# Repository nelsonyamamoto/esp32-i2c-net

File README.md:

# esp32-i2c-net

An ESP32-S3 based IoT data collector with buffered I2C bus over standard
6P6C (RJ12/RJ25) cables, so multiple remote I2C nodes can be wired back to a
single controller using cheap, keyed telephone-style patch cords. The use of
I2C bus driver allow the connection of multiple sensor over long wires.

## Hardware

- **MCU:** ESP32-S3-WROOM-1 (U1)
- **I2C buffering:** PCA9517 level-shifting I2C repeater (U4) plus an
  LTC4311 active rise-time accelerator (U3) to keep edges clean over long
  cable runs
- **Bus ports:** 4× 6P6C modular jacks (J3–J6)
- **USB:** USB-A connector (J1) wired to the ESP32-S3 native USB pins
  (GPIO19 = D−, GPIO20 = D+) for connection of an optional USB device, like a camera.
- **Power:** +5 V input via barrel jack (J2) or USB; AMS1117-3.3 LDO (U2)
  provides the +3.3 V rail
- **Indicators / misc:** WS2812B addressable RGB LED (D1, data on GPIO38),
  reset pushbutton (SW1 on EN), 3.3 V test point (TP1), auxiliary 1×6 header
  (J7) exposing spare GPIOs

### 6P6C port pinout (J3–J6)

| Pin | Signal     |
|-----|------------|
| 1   | GND        |
| 2   | SDA        |
| 3   | +5 V       |
| 4   | +5 V       |
| 5   | SCL        |
| 6   | GND        |
| SH  | Shield/GND |

The buffered bus on the jacks runs at 5 V logic levels (PCA9517 A-side at
+5 V with pull-ups R4/R5); the ESP32 side of the repeater runs at 3.3 V
(GPIO1 = SDA, GPIO2 = SCL, pull-ups R1/R2/R3). The PCA9517 also isolates
the cable capacitance from the MCU bus.

## Repository contents

| File                    | Description                                  |
|-------------------------|----------------------------------------------|
| `esp32-i2c-net.kicad_pro`  | KiCad 7 project file                      |
| `esp32-i2c-net.kicad_sch`  | Schematic                                 |
| `esp32-i2c-net.kicad_pcb`  | PCB layout                                |

## Requirements

- KiCad 7 or later (files use the KiCad 7 schematic/PCB format)

## Status

Work in progress — schematic complete, PCB layout in progress
(DSN exports for the Freerouting autorouter are included).
No firmware in this repository.

## License

No license file is currently included; the design files are provided as-is.

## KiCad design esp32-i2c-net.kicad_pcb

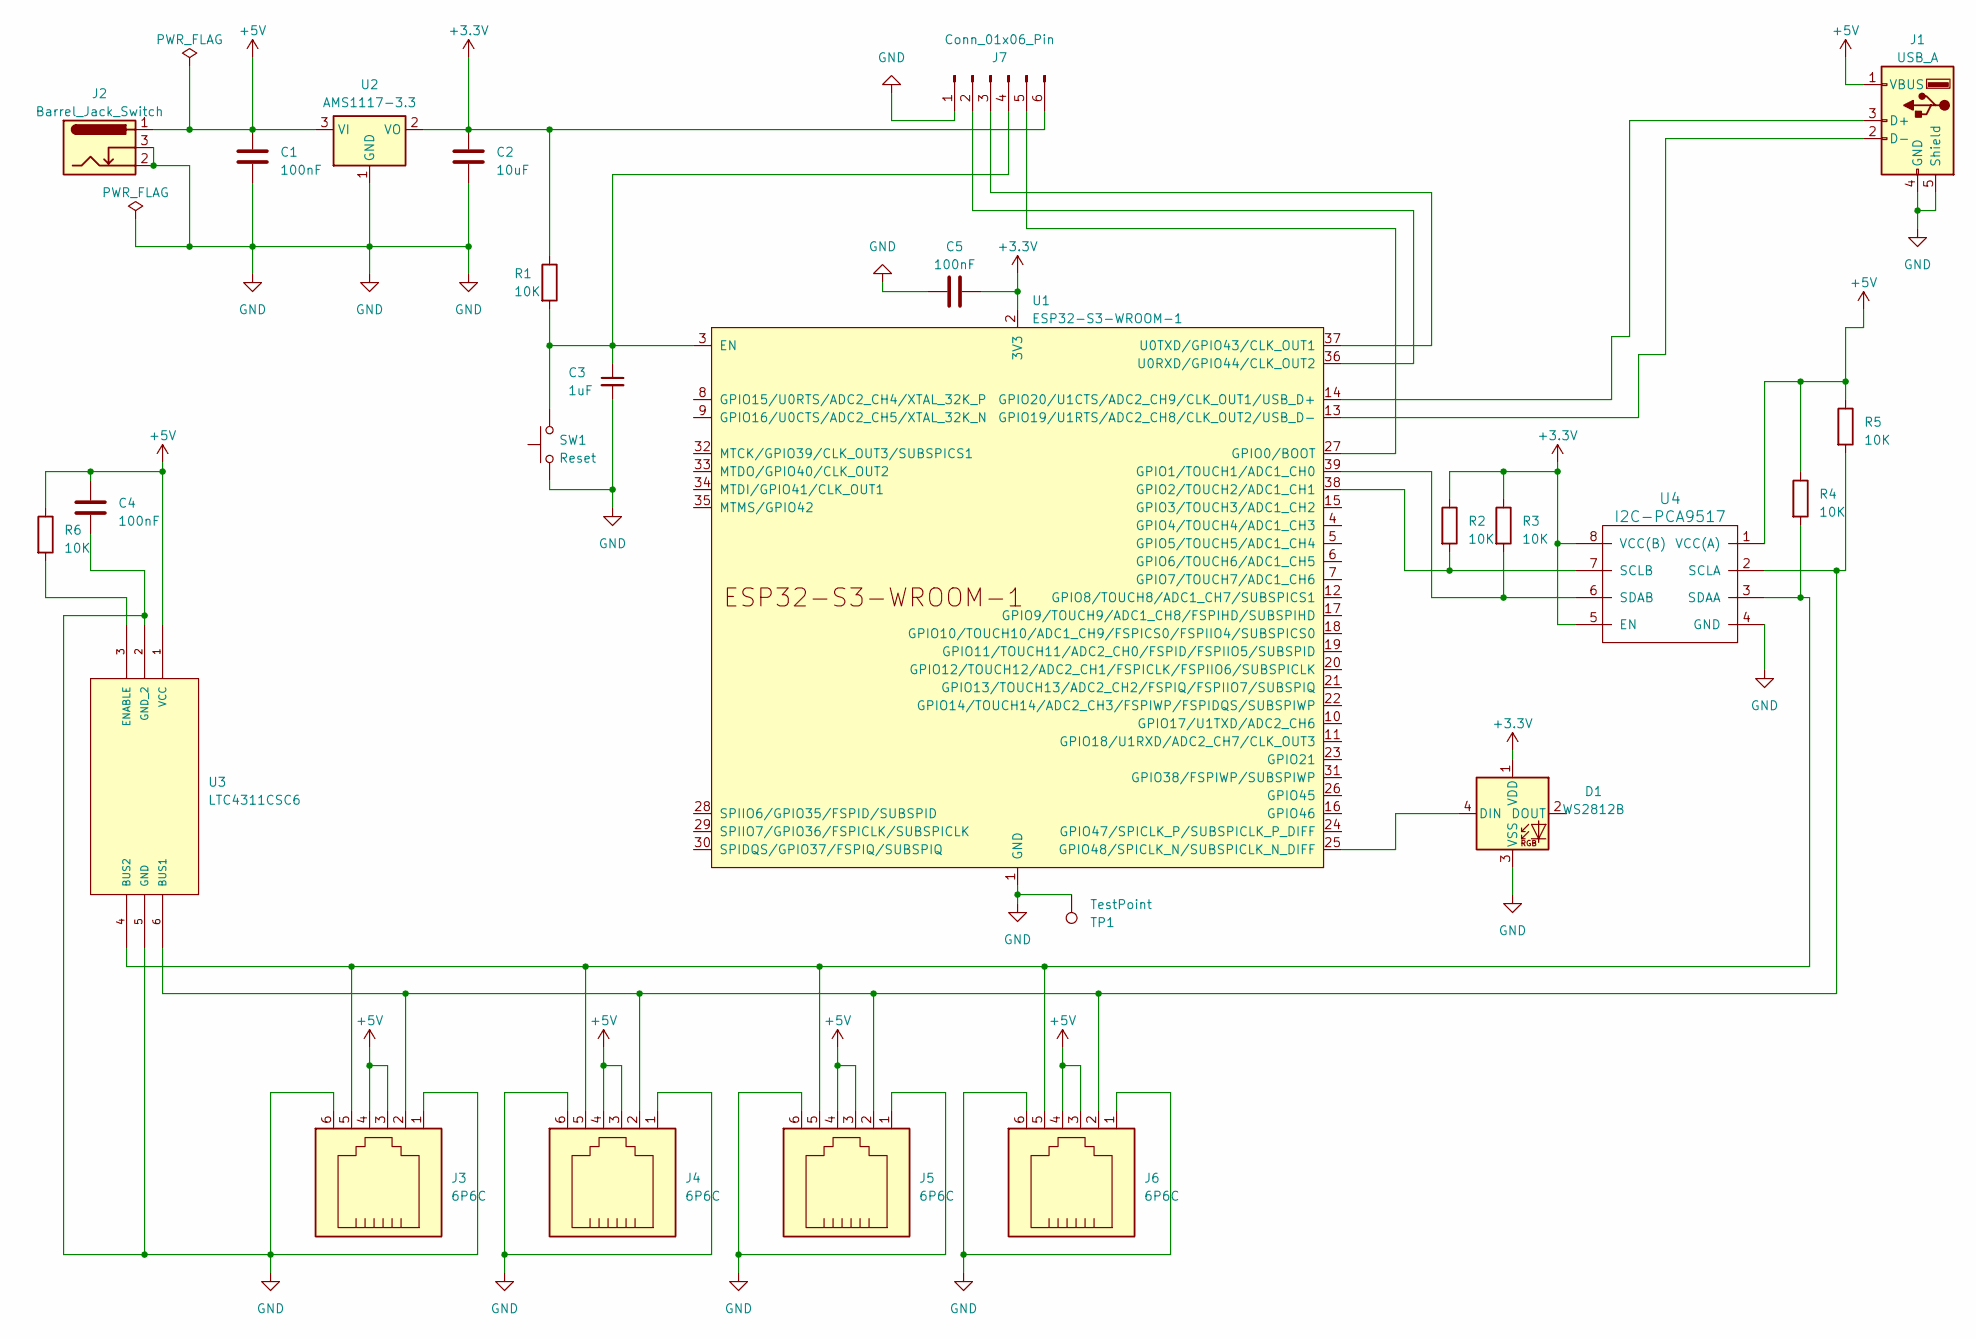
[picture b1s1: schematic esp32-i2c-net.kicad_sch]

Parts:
C1, C4, C5: 100nF; C_0805_2012Metric_Pad1.18x1.45mm_HandSolder
C2: 10uF; C_0805_2012Metric_Pad1.18x1.45mm_HandSolder
C3: 1uF; C_0805_2012Metric_Pad1.18x1.45mm_HandSolder
D1: WS2812B; LED_WS2812B_PLCC4_5.0x5.0mm_P3.2mm
J1: USB_A; USB_A_Wuerth_614004134726_Horizontal
J2: Barrel_Jack_Switch; BarrelJack_Horizontal
J3, J4, J5, J6: 6P6C; RJ12_Amphenol_54601
J7: Conn_01x06_Pin; PinHeader_1x06_P2.54mm_Vertical
R1, R2, R3, R4, R5, R6: 10K; R_0805_2012Metric_Pad1.20x1.40mm_HandSolder
SW1: Reset; SW_Tactile_SPST_NO_Straight_CK_PTS636Sx25SMTRLFS
TP1: TestPoint; TestPoint_Plated_Hole_D3.0mm
U1: ESP32-S3-WROOM-1
U2: AMS1117-3.3; SOT-223-3_TabPin2
U3: LTC4311CSC6; SOT-363_SC-70-6_Handsoldering; MANUFACTURER_PART_NUMBER ltc4311csc6#pbf
U4: I2C-PCA9517; TSSOP-8_4.4x3mm_P0.65mm

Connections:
+3.3V: C2.1, C5.2, D1.1 (VDD), J7.6, R1.1, R2.1, R3.1, U1.2 (3V3), U2.2 (VO), U4.5 (EN), U4.8 (VCC(B))
+5V: C1.1, C4.1, J1.1 (VBUS), J2.1, J3.3, J3.4, J4.3, J4.4, J5.3, J5.4, J6.3, J6.4, R4.1, R5.1, R6.1, U2.3 (VI), U3.1 (VCC), U4.1 (VCC(A))
GND: C1.2, C2.2, C3.2, C4.2, C5.1, D1.3 (VSS), J1.4 (GND), J1.5 (Shield), J2.2, J2.3, J3.1, J3.6, J4.1, J4.6, J5.1, J5.6, J6.1, J6.6, J7.1, SW1.1, TP1.1, U1.1 (GND), U1.40 (GND), U1.41 (GND), U2.1 (GND), U3.2 (GND_2), U3.5 (GND), U4.4 (GND)
unnamed: D1.4 (DIN), U1.25 (GPIO48/SPICLK_N/SUBSPICLK_N_DIFF)
unnamed: J1.3 (D+), U1.14 (GPIO20/U1CTS/ADC2_CH9/CLK_OUT1/USB_D+)
unnamed: J1.2 (D-), U1.13 (GPIO19/U1RTS/ADC2_CH8/CLK_OUT2/USB_D-)
unnamed: J7.2, U1.36 (U0RXD/GPIO44/CLK_OUT2)
unnamed: J7.3, U1.37 (U0TXD/GPIO43/CLK_OUT1)
unnamed: C3.1, J7.4, R1.2, SW1.2, U1.3 (EN)
unnamed: J7.5, U1.27 (GPIO0/BOOT)
unnamed: R3.2, U1.39 (GPIO1/TOUCH1/ADC1_CH0), U4.6 (SDAB)
unnamed: R2.2, U1.38 (GPIO2/TOUCH2/ADC1_CH1), U4.7 (SCLB)
unnamed: J3.2, J4.2, J5.2, J6.2, R5.2, U3.6 (BUS1), U4.2 (SCLA)
unnamed: J3.5, J4.5, J5.5, J6.5, R4.2, U3.4 (BUS2), U4.3 (SDAA)
unnamed: R6.2, U3.3 (ENABLE)

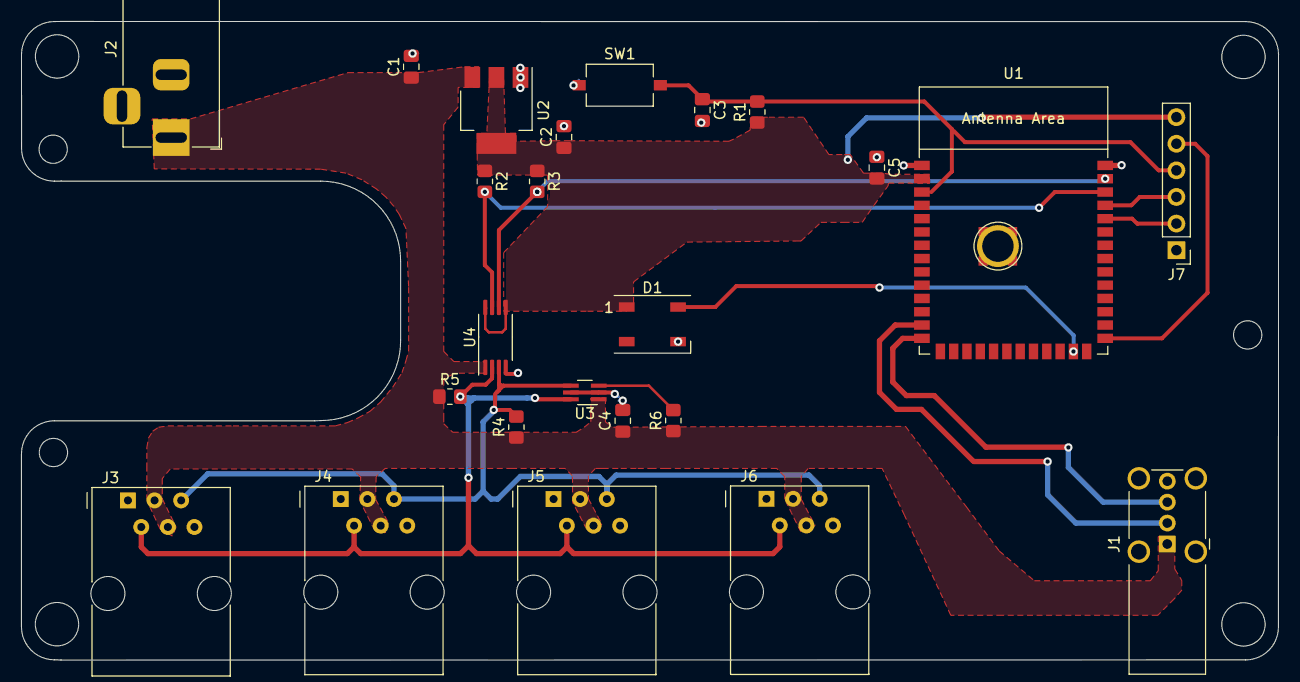
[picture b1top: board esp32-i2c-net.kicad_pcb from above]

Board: 2 copper layers, 120.0 x 61.0 mm, 25 parts (0 on the bottom side), 15 nets.

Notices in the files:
parts and their libraries:
COPYRIGHT: Copyright C 2016 Accelerated Designs. All rights reserved
